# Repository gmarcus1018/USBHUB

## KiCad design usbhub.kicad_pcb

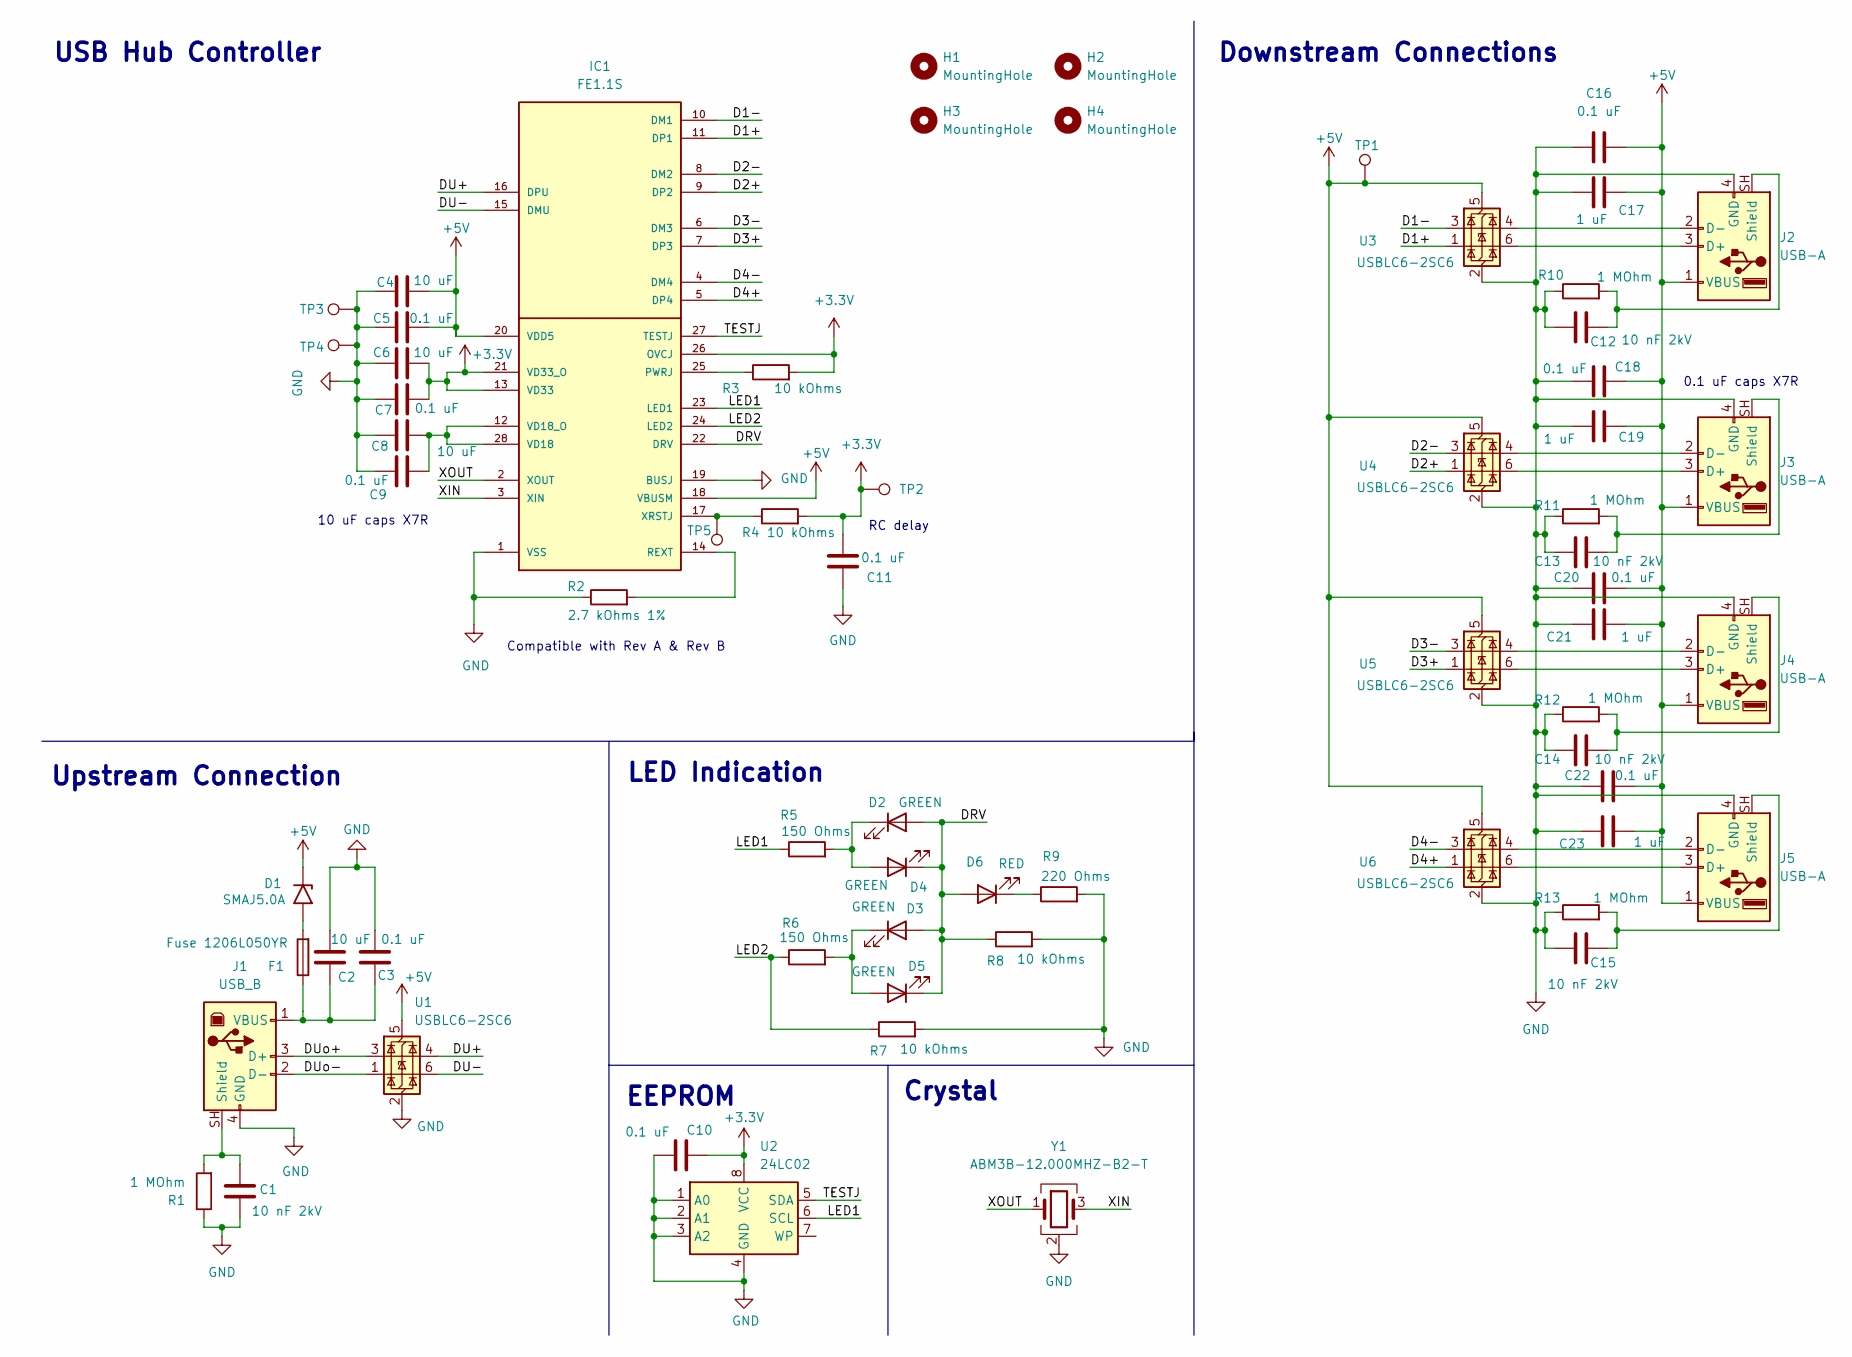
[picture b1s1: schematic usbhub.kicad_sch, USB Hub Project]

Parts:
C1, C12, C13, C14, C15: 10 nF 2kV; C_0402_1005Metric
C2, C4, C6, C8: 10 uF; C_0402_1005Metric
C3, C5, C7, C9, C10, C11, C16, C18, C20, C22: 0.1 uF; C_0402_1005Metric
C17, C19, C21, C23: 1 uF; C_0603_1608Metric
D1: SMAJ5.0A; D_SMA
D2, D3, D4, D5: GREEN; LED_0603_1608Metric
D6: RED; LED_0603_1608Metric
F1: Fuse 1206L050YR; Fuse_1206_3216Metric
H1, H2, H3, H4: MountingHole; MountingHole_2.2mm_M2
IC1: FE1.1S; SOP64P600X175-28N
J1: USB_B; CUI_UJ2-BH-W1-TH
J2, J3, J4, J5: USB-A; USB_A_Kycon_KUSBX-AS1N-B_Horizontal; PARTREV E
R1, R10, R11, R12, R13: 1 MOhm; R_0402_1005Metric
R2: 2.7 kOhms 1%; R_0402_1005Metric
R3, R4, R7, R8: 10 kOhms; R_0402_1005Metric
R5, R6: 150 Ohms; R_0402_1005Metric
R9: 220 Ohms; R_0402_1005Metric
TP1, TP2, TP3, TP4, TP5: TestPoint; TestPoint_Pad_D1.0mm
U1, U3, U4, U5, U6: USBLC6-2SC6; SOT-23-6
U2: 24LC02; SOIC-8-1EP_3.9x4.9mm_P1.27mm_EP2.29x3mm
Y1: ABM3B-12.000MHZ-B2-T; Crystal_SMD_Abracon_ABM3B-4Pin_5.0x3.2mm

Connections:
+3.3V: C6.2, C7.2, C10.1, C11.2, IC1.13 (VD33), IC1.21 (VD33_O), IC1.26 (OVCJ), R3.2, R4.2, TP2.1 (1_1), U2.8 (VCC)
+5V: C4.2, C5.2, C16.2, C17.2, C18.2, C19.2, C20.2, C21.2, C22.2, C23.2, D1.1 (A1), IC1.18 (VBUSM), IC1.20 (VDD5), J2.1 (VBUS), J3.1 (VBUS), J4.1 (VBUS), J5.1 (VBUS), TP1.1 (1_1), U1.5 (VBUS), U3.5 (VBUS), U4.5 (VBUS), U5.5 (VBUS), U6.5 (VBUS)
/D1+: IC1.11 (DP1), U3.1 (I/O2)
/D1-: IC1.10 (DM1), U3.3 (I/O1)
/D2+: IC1.9 (DP2), U4.1 (I/O2)
/D2-: IC1.8 (DM2), U4.3 (I/O1)
/D3+: IC1.7 (DP3), U5.1 (I/O2)
/D3-: IC1.6 (DM3), U5.3 (I/O1)
/D4+: IC1.5 (DP4), U6.1 (I/O2)
/D4-: IC1.4 (DM4), U6.3 (I/O1)
/DRV: D2.2 (A), D3.2 (A), D4.1 (K), D5.1 (K), D6.2 (A), IC1.22 (DRV), R8.1
/DU+: IC1.16 (DPU), U1.4 (I/O1)
/DU-: IC1.15 (DMU), U1.6 (I/O2)
/DUo+: J1.3 (D+), U1.3 (I/O1)
/DUo-: J1.2 (D-), U1.1 (I/O2)
/LED1: IC1.23 (LED1), R5.1, U2.6 (SCL)
/LED2: IC1.24 (LED2), R6.1, R7.1
/TESTJ: IC1.27 (TESTJ), U2.5 (SDA)
/XIN: IC1.3 (XIN), Y1.3
/XOUT: IC1.2 (XOUT), Y1.1
GND: C1.1, C2.2, C3.2, C4.1, C5.1, C6.1, C7.1, C8.1, C9.1, C10.2, C11.1, C12.1, C13.1, C14.1, C15.1, C16.1, C17.1, C18.1, C19.1, C20.1, C21.1, C22.1, C23.1, IC1.1 (VSS), IC1.19 (BUSJ), J1.4 (GND), J2.4 (GND), J3.4 (GND), J4.4 (GND), J5.4 (GND), R1.1, R2.1, R7.2, R8.2, R9.2, R10.1, R11.1, R12.1, R13.1, TP3.1 (1_1), TP4.1 (1_1), U1.2 (GND), U2.1 (A0), U2.2 (A1), U2.3 (A2), U2.4 (GND), U3.2 (GND), U4.2 (GND), U5.2 (GND), U6.2 (GND), Y1.2 (G), Y1.4 (G)
unnamed: D1.2 (A2), F1.2
unnamed: D2.1 (K), D4.2 (A), R5.2
unnamed: D3.1 (K), D5.2 (A), R6.2
unnamed: D6.1 (K), R9.1
unnamed: IC1.25 (PWRJ), R3.1
unnamed: IC1.14 (REXT), R2.2
unnamed: C8.2, C9.2, IC1.12 (VD18_O), IC1.28 (VD18)
unnamed: IC1.17 (XRSTJ), R4.1, TP5.1 (1_1)
unnamed: C1.2, J1.SH (Shield), R1.2
unnamed: C2.1, C3.1, F1.1, J1.1 (VBUS)
unnamed: J2.3 (D+), U3.6 (I/O2)
unnamed: J2.2 (D-), U3.4 (I/O1)
unnamed: C12.2, J2.SH (Shield), R10.2
unnamed: J3.3 (D+), U4.6 (I/O2)
unnamed: J3.2 (D-), U4.4 (I/O1)
unnamed: C13.2, J3.SH (Shield), R11.2
unnamed: J4.3 (D+), U5.6 (I/O2)
unnamed: J4.2 (D-), U5.4 (I/O1)
unnamed: C14.2, J4.SH (Shield), R12.2
unnamed: J5.3 (D+), U6.6 (I/O2)
unnamed: J5.2 (D-), U6.4 (I/O1)
unnamed: C15.2, J5.SH (Shield), R13.2

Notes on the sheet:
Compatible with Rev A & Rev B
RC delay
EEPROM
0.1 uF caps X7R
10 uF caps X7R
USB Hub Controller
LED Indication
Upstream Connection
Downstream Connections
Crystal

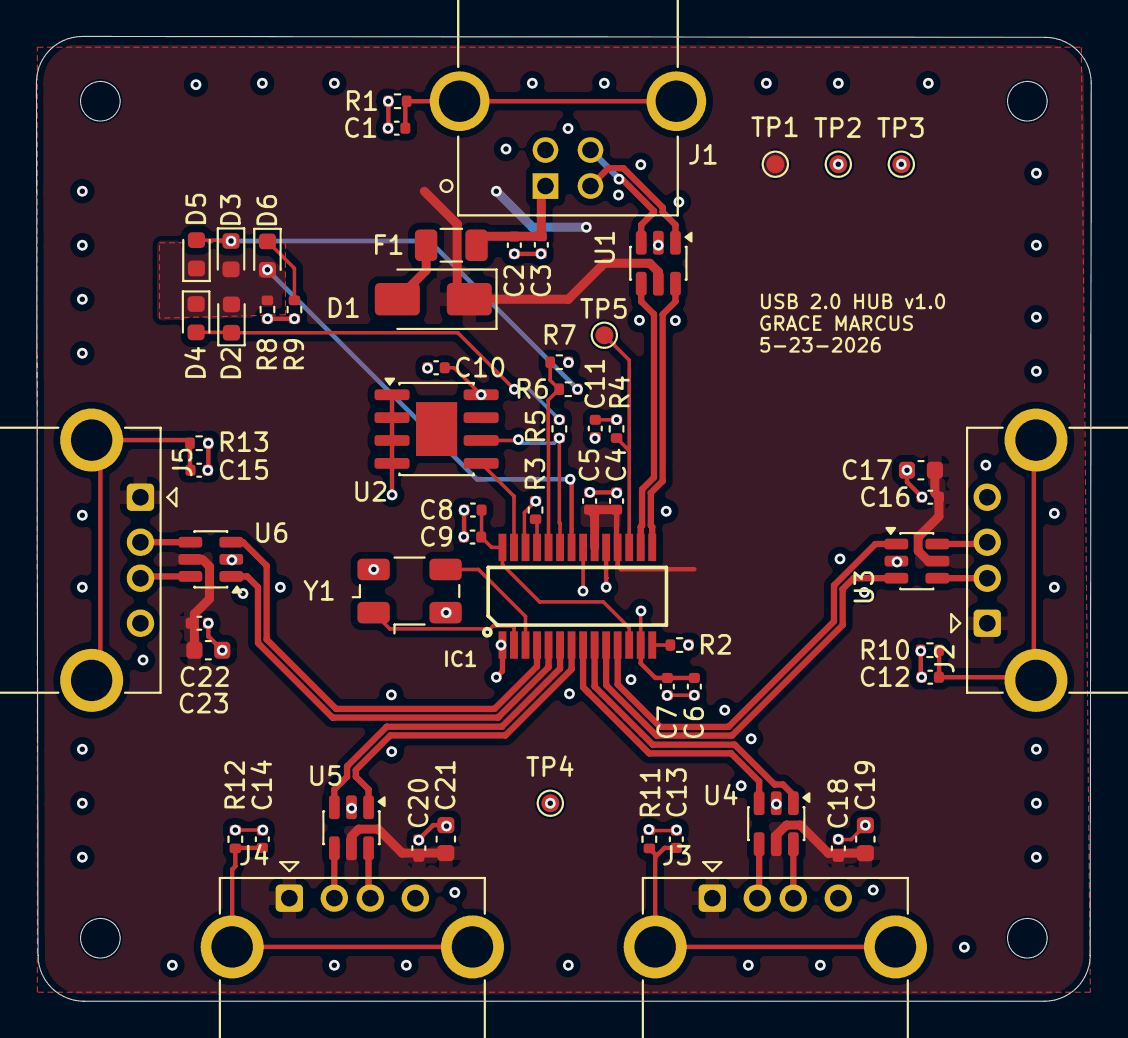
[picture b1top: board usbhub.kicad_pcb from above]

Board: 4 copper layers, 58.6 x 53.6 mm, 65 parts (0 on the bottom side), 43 nets.

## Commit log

2026-06-19 USB connectors 3D model update
2026-06-20 add FE1.1s 3D model
2026-06-26 X7R -> X5R
